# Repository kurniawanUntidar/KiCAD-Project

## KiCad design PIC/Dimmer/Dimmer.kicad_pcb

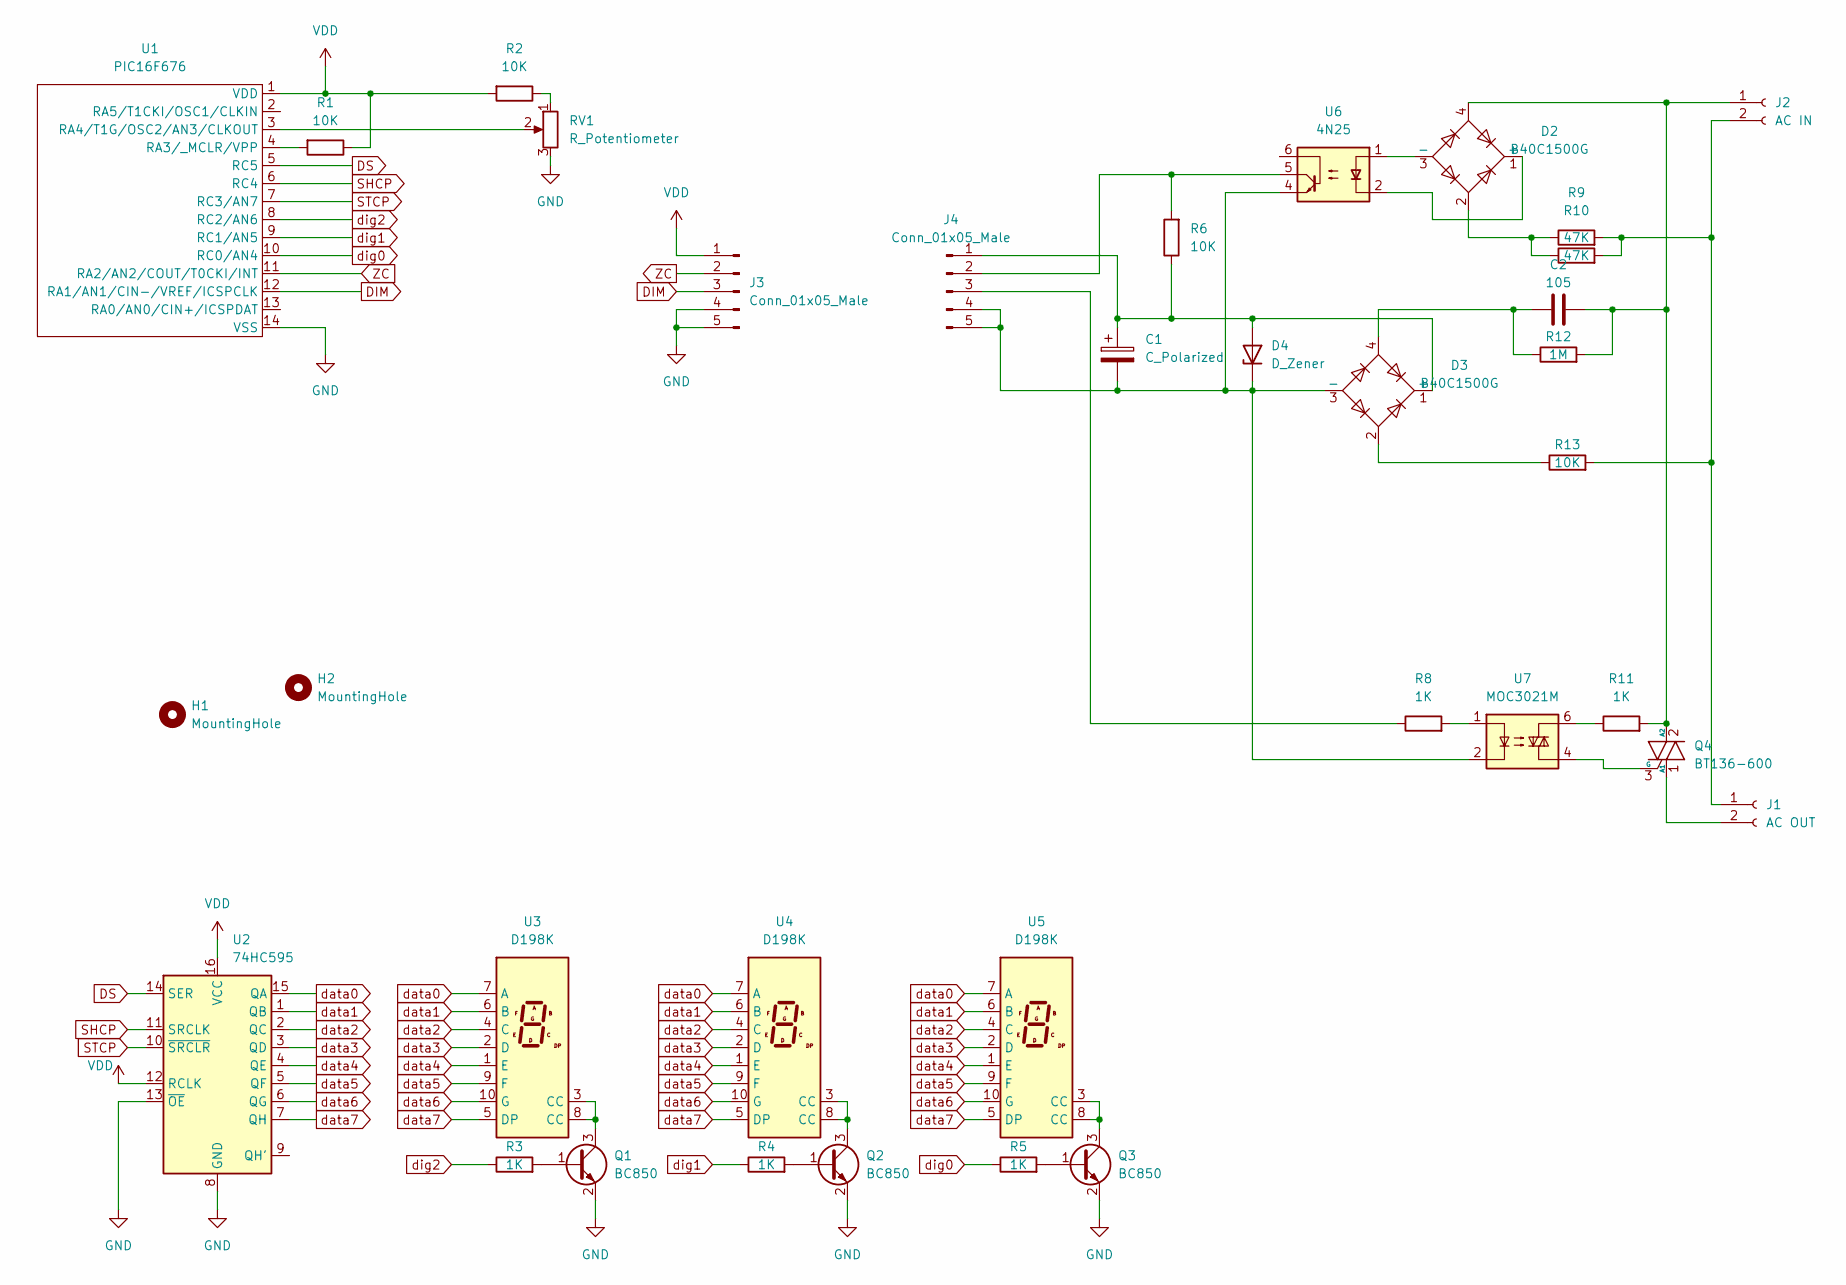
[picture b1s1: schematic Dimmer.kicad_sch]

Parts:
C1: C_Polarized; CP_Radial_D6.3mm_P2.50mm
C2: 105; C_Axial_L5.1mm_D3.1mm_P12.50mm_Horizontal
D2, D3: B40C1500G; Diode_Bridge_Round_D9.8mm
D4: D_Zener; D_DO-34_SOD68_P7.62mm_Horizontal
H1, H2: MountingHole; MountingHole_2.5mm_Pad_Via
J1: AC OUT; TerminalBlock_Phoenix_MKDS-1,5-2_1x02_P5.00mm_Horizontal
J2: AC IN; TerminalBlock_Phoenix_MKDS-1,5-2_1x02_P5.00mm_Horizontal
J3, J4: Conn_01x05_Male; PinHeader_1x05_P2.54mm_Vertical
Q1, Q2, Q3: BC850; SOT-23
Q4: BT136-600; TO-220-3_Vertical
R1, R2, R6: 10K; R_1206_3216Metric
R3, R4, R5, R8, R11: 1K; R_1206_3216Metric
R9, R10: 47K; R_1206_3216Metric
R12: 1M; R_Axial_DIN0204_L3.6mm_D1.6mm_P7.62mm_Horizontal
R13: 10K; R_Axial_DIN0204_L3.6mm_D1.6mm_P7.62mm_Horizontal
RV1: R_Potentiometer; Potentiometer_Bourns_3266Z_Horizontal
U1: PIC16F676; SOIC-14_3.9x8.7mm_P1.27mm
U2: 74HC595; SOIC-16_3.9x9.9mm_P1.27mm
U3, U4, U5: D198K; D1X8K
U6: 4N25; DIP-6_W7.62mm
U7: MOC3021M; DIP-6_W7.62mm

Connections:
DIM: J3.3, U1.12 (RA1/AN1/CIN-/VREF/ICSPCLK)
DS: U1.5 (RC5), U2.14 (SER)
GND: J3.4, J3.5, Q1.2 (E), Q2.2 (E), Q3.2 (E), RV1.3, U1.14 (VSS), U2.8 (GND), U2.13 (~OE)
unnamed: C1.1, D3.1 (+), D4.2 (A), J4.1, R6.1
unnamed: C1.2, D3.3 (-), D4.1 (K), J4.4, J4.5, U6.4, U7.2
unnamed: C2.1, D3.4, R12.1
unnamed: C2.2, D2.4, J2.1, Q4.2 (A2), R11.2, R12.2
unnamed: D2.1 (+), U6.2
unnamed: D2.2, R9.1, R10.1
unnamed: D2.3 (-), U6.1
unnamed: D3.2, R13.1
unnamed: J1.1, J2.2, R9.2, R10.2, R13.2
unnamed: J1.2, Q4.1 (A1)
unnamed: J4.2, R6.2, U6.5
unnamed: J4.3, R8.1
unnamed: Q1.1 (B), R3.2
unnamed: Q1.3 (C), U3.3 (CC), U3.8 (CC)
unnamed: Q2.1 (B), R4.2
unnamed: Q2.3 (C), U4.3 (CC), U4.8 (CC)
unnamed: Q3.1 (B), R5.2
unnamed: Q3.3 (C), U5.3 (CC), U5.8 (CC)
unnamed: Q4.3 (G), U7.4
unnamed: R1.2, U1.4 (RA3/_MCLR/VPP)
unnamed: R2.1, RV1.1
unnamed: R8.2, U7.1
unnamed: R11.1, U7.6
unnamed: RV1.2, U1.3 (RA4/T1G/OSC2/AN3/CLKOUT)
SHCP: U1.6 (RC4), U2.11 (SRCLK)
STCP: U1.7 (RC3/AN7), U2.10 (~SRCLR)
VDD: J3.1, R1.1, R2.2, U1.1 (VDD), U2.12 (RCLK), U2.16 (VCC)
ZC: J3.2, U1.11 (RA2/AN2/COUT/T0CKI/INT)
data0: U2.15 (QA), U3.7 (A), U4.7 (A), U5.7 (A)
data1: U2.1 (QB), U3.6 (B), U4.6 (B), U5.6 (B)
data2: U2.2 (QC), U3.4 (C), U4.4 (C), U5.4 (C)
data3: U2.3 (QD), U3.2 (D), U4.2 (D), U5.2 (D)
data4: U2.4 (QE), U3.1 (E), U4.1 (E), U5.1 (E)
data5: U2.5 (QF), U3.9 (F), U4.9 (F), U5.9 (F)
data6: U2.6 (QG), U3.10 (G), U4.10 (G), U5.10 (G)
data7: U2.7 (QH), U3.5 (DP), U4.5 (DP), U5.5 (DP)
dig0: R5.1, U1.10 (RC0/AN4)
dig1: R4.1, U1.9 (RC1/AN5)
dig2: R3.1, U1.8 (RC2/AN6)

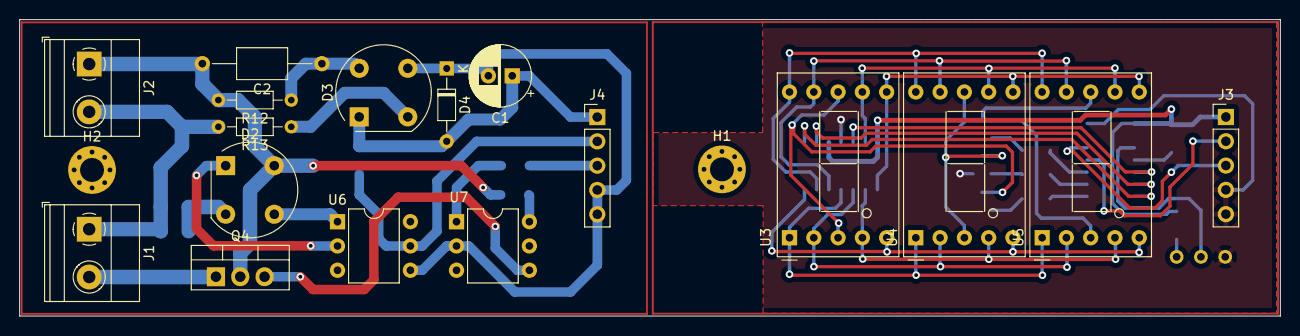
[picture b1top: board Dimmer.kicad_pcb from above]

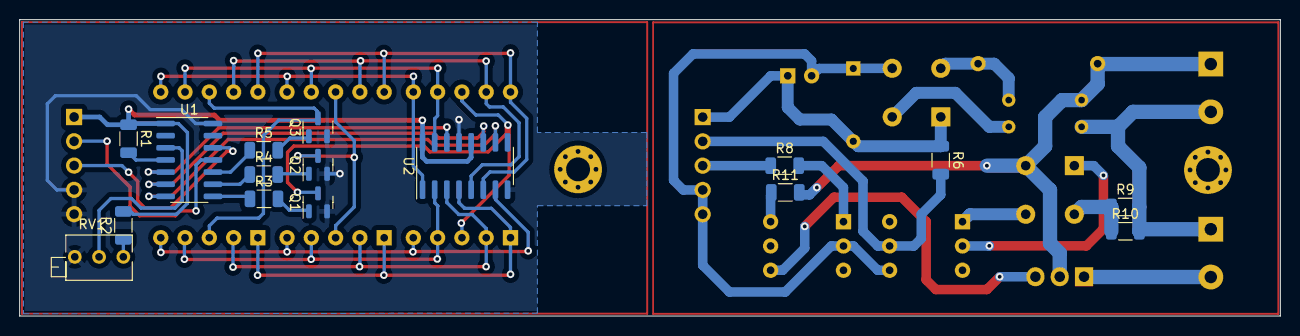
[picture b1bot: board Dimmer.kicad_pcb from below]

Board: 2 copper layers, 131.8 x 31.0 mm, 35 parts (16 on the bottom side), 42 nets.

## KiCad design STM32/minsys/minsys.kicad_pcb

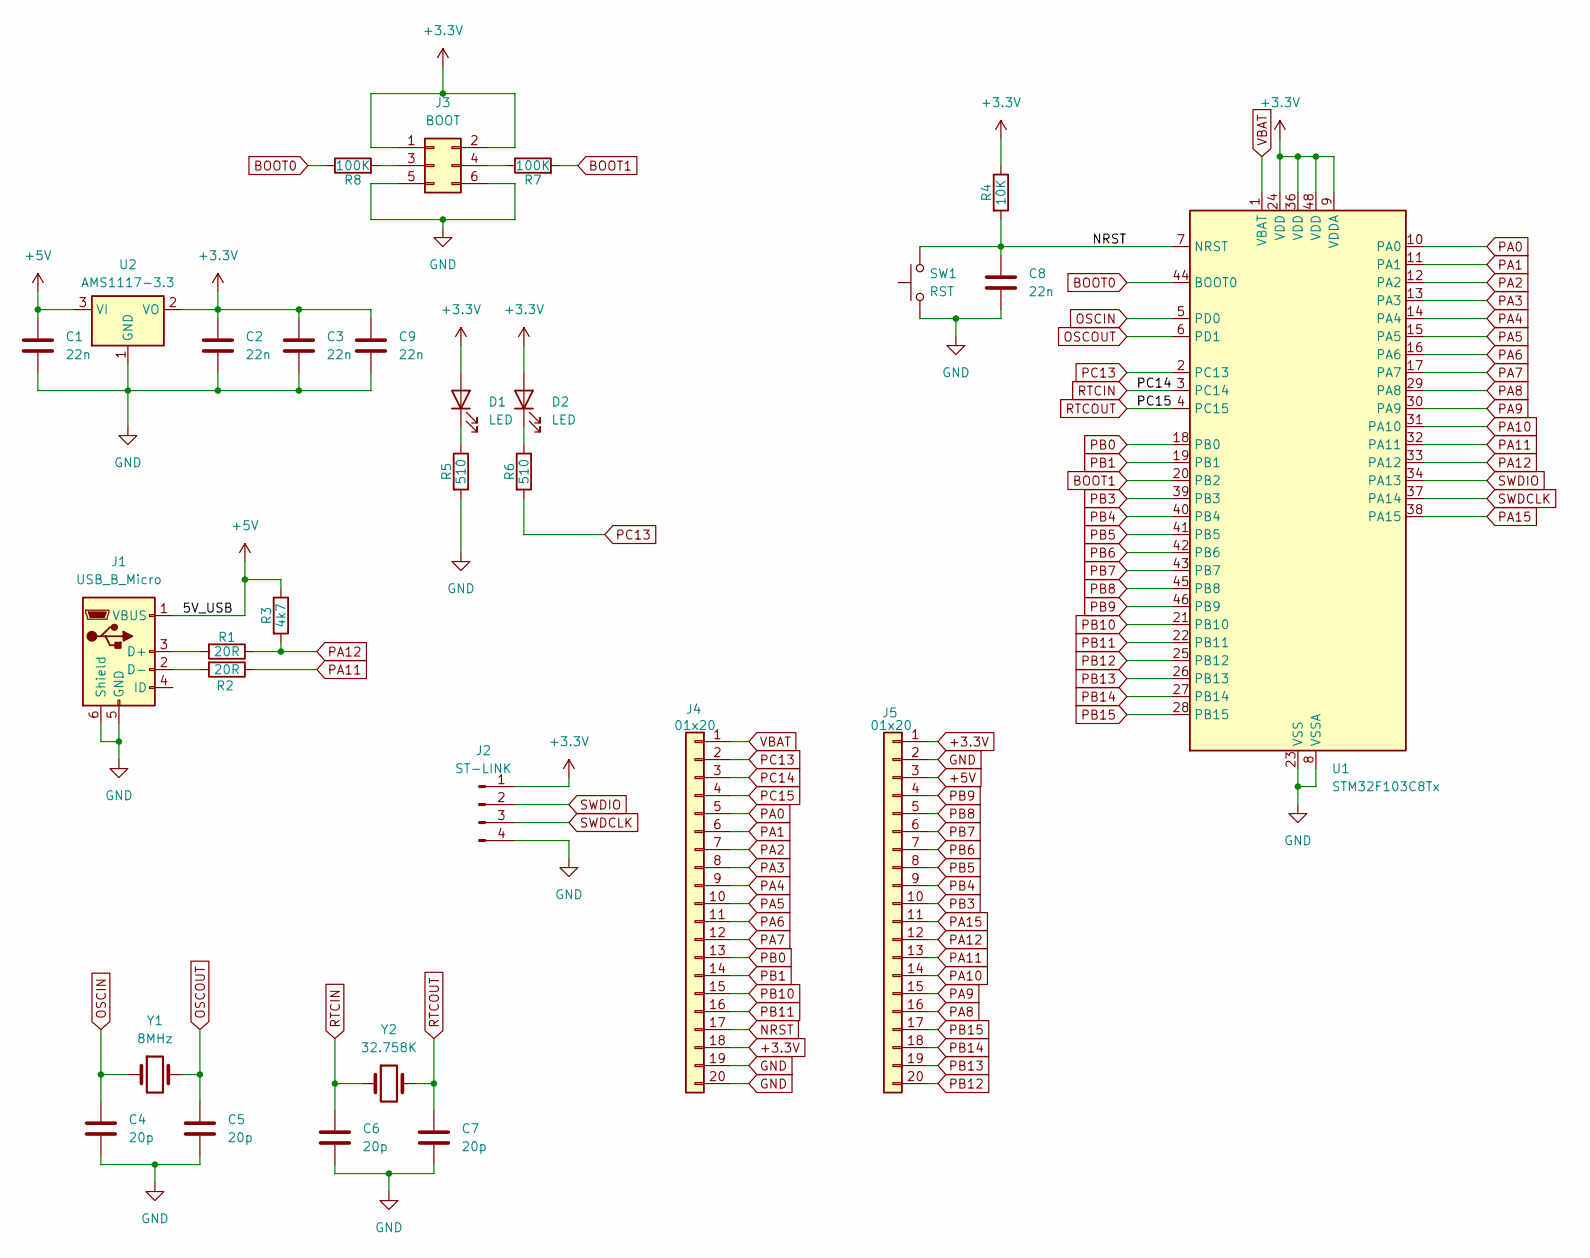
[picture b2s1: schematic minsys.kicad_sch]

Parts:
C1, C2, C3, C8, C9: 22n; C_1206_3216Metric_Pad1.33x1.80mm_HandSolder
C4, C5, C6, C7: 20p; C_1206_3216Metric_Pad1.33x1.80mm_HandSolder
D1, D2: LED; LED_0402_1005Metric_Pad0.77x0.64mm_HandSolder
J1: USB_B_Micro; USB_Micro-B_Amphenol_10118193-0001LF_Horizontal
J2: ST-LINK; JST_EH_B4B-EH-A_1x04_P2.50mm_Vertical
J3: BOOT; PinHeader_2x03_P2.54mm_Vertical
J4, J5: 01x20; PinHeader_1x20_P2.54mm_Vertical
R1, R2: 20R; R_1206_3216Metric_Pad1.30x1.75mm_HandSolder
R3: 4k7; R_1206_3216Metric_Pad1.30x1.75mm_HandSolder
R4: 10K; R_1206_3216Metric_Pad1.30x1.75mm_HandSolder
R5, R6: 510; R_1206_3216Metric_Pad1.30x1.75mm_HandSolder
R7, R8: 100K; R_1206_3216Metric_Pad1.30x1.75mm_HandSolder
SW1: RST; SW_Push_1P1T_NO_CK_KSC6xxG
U1: STM32F103C8Tx; LQFP-48_7x7mm_P0.5mm
U2: AMS1117-3.3; SOT-223-3_TabPin2
Y1: 8MHz; Crystal_HC18-U_Vertical
Y2: 32.758K; Crystal_DS26_D2.0mm_L6.0mm_Horizontal

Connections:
+3.3V: C2.1, C3.1, C9.1, D1.2 (A), D2.2 (A), J2.1, J3.1, J3.2, J4.18, J5.1, R4.1, U1.9 (VDDA), U1.24 (VDD), U1.36 (VDD), U1.48 (VDD), U2.2 (VO)
+5V: C1.1, J1.1 (VBUS), J5.3, R3.1, U2.3 (VI)
BOOT0: R8.1, U1.44 (BOOT0)
BOOT1: R7.2, U1.20 (PB2)
GND: C1.2, C2.2, C3.2, C4.2, C5.2, C6.2, C7.2, C8.2, C9.2, J1.5 (GND), J1.6 (Shield), J2.4, J3.5, J3.6, J4.19, J4.20, J5.2, R5.2, SW1.1, U1.8 (VSSA), U1.23 (VSS), U1.35 (VSS), U1.47 (VSS), U2.1 (GND)
NRST: C8.1, J4.17, R4.2, SW1.2, U1.7 (NRST)
unnamed: D1.1 (K), R5.1
unnamed: D2.1 (K), R6.1
unnamed: J1.3 (D+), R1.2
unnamed: J1.2 (D-), R2.2
unnamed: J3.3, R8.2
unnamed: J3.4, R7.1
OSCIN: C4.1, U1.5 (PD0), Y1.1
OSCOUT: C5.1, U1.6 (PD1), Y1.2
PA0: J4.5, U1.10 (PA0)
PA1: J4.6, U1.11 (PA1)
PA2: J4.7, U1.12 (PA2)
PA3: J4.8, U1.13 (PA3)
PA4: J4.9, U1.14 (PA4)
PA5: J4.10, U1.15 (PA5)
PA6: J4.11, U1.16 (PA6)
PA7: J4.12, U1.17 (PA7)
PA8: J5.16, U1.29 (PA8)
PA9: J5.15, U1.30 (PA9)
PA10: J5.14, U1.31 (PA10)
PA11: J5.13, R2.1, U1.32 (PA11)
PA12: J5.12, R1.1, R3.2, U1.33 (PA12)
PA15: J5.11, U1.38 (PA15)
PB0: J4.13, U1.18 (PB0)
PB1: J4.14, U1.19 (PB1)
PB3: J5.10, U1.39 (PB3)
PB4: J5.9, U1.40 (PB4)
PB5: J5.8, U1.41 (PB5)
PB6: J5.7, U1.42 (PB6)
PB7: J5.6, U1.43 (PB7)
PB8: J5.5, U1.45 (PB8)
PB9: J5.4, U1.46 (PB9)
PB10: J4.15, U1.21 (PB10)
PB11: J4.16, U1.22 (PB11)
PB12: J5.20, U1.25 (PB12)
PB13: J5.19, U1.26 (PB13)
PB14: J5.18, U1.27 (PB14)
PB15: J5.17, U1.28 (PB15)
PC13: J4.2, R6.2, U1.2 (PC13)
PC14: C6.1, J4.3, U1.3 (PC14), Y2.1
PC15: C7.1, J4.4, U1.4 (PC15), Y2.2
SWDCLK: J2.3, U1.37 (PA14)
SWDIO: J2.2, U1.34 (PA13)
VBAT: J4.1, U1.1 (VBAT)

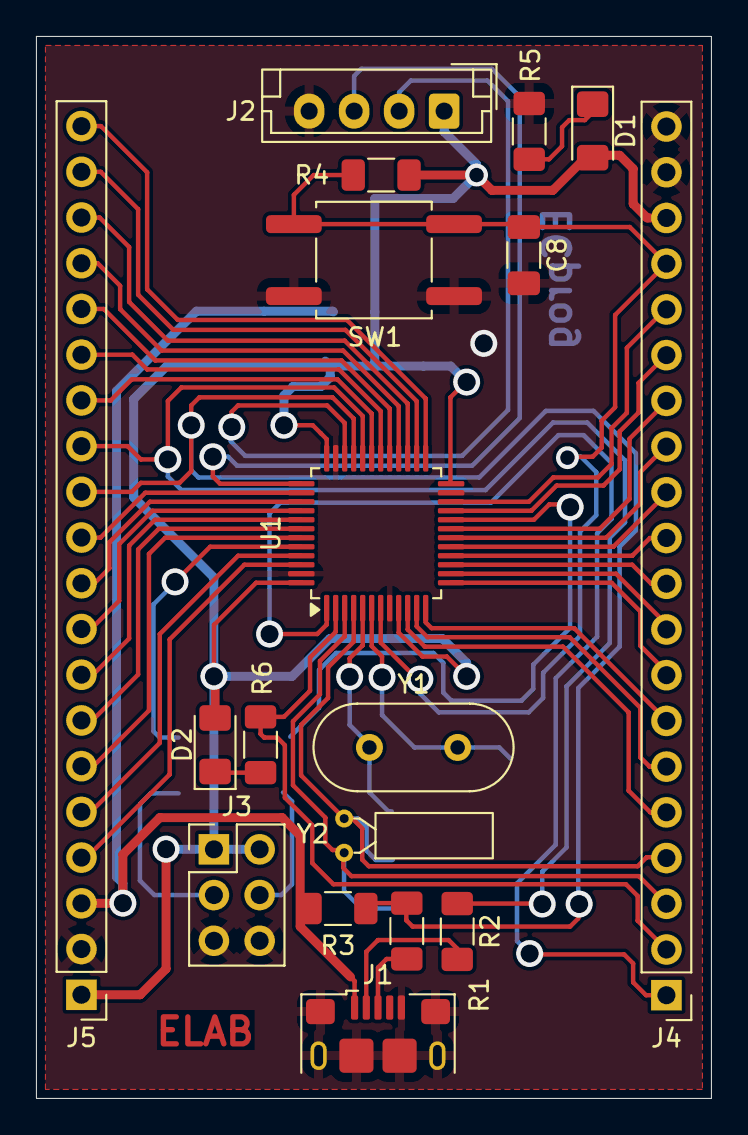
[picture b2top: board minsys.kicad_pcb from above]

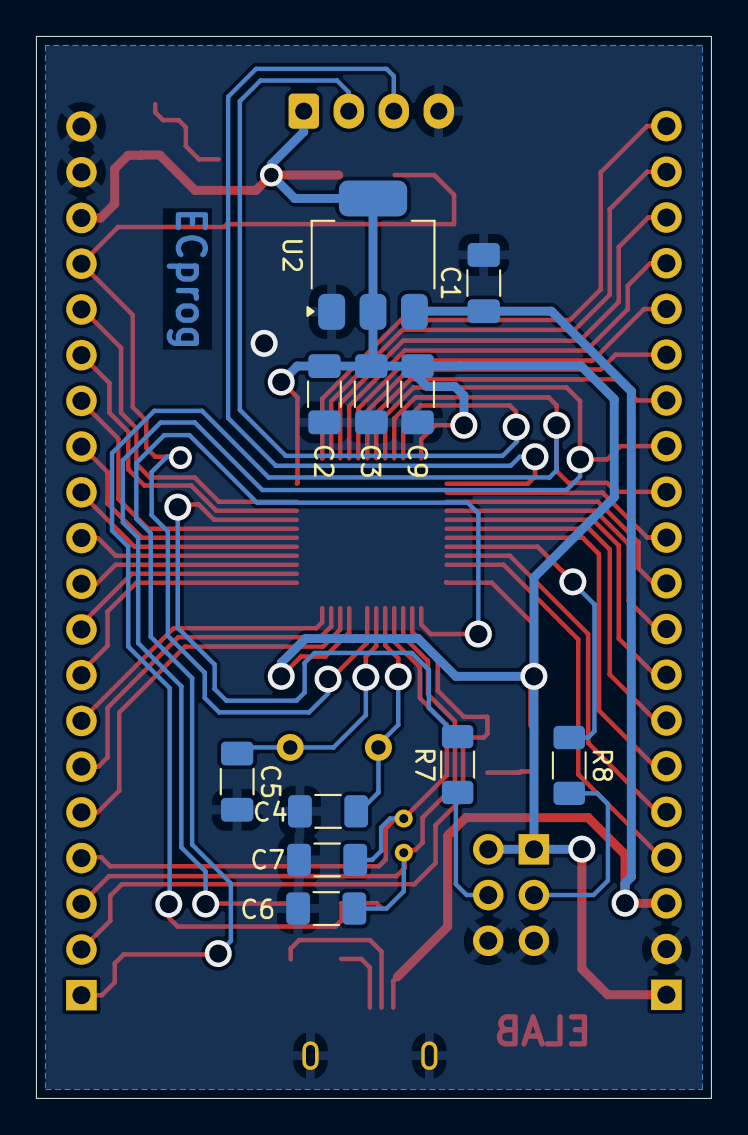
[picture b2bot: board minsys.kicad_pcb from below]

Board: 2 copper layers, 37.5 x 59.0 mm, 29 parts (11 on the bottom side), 49 nets.

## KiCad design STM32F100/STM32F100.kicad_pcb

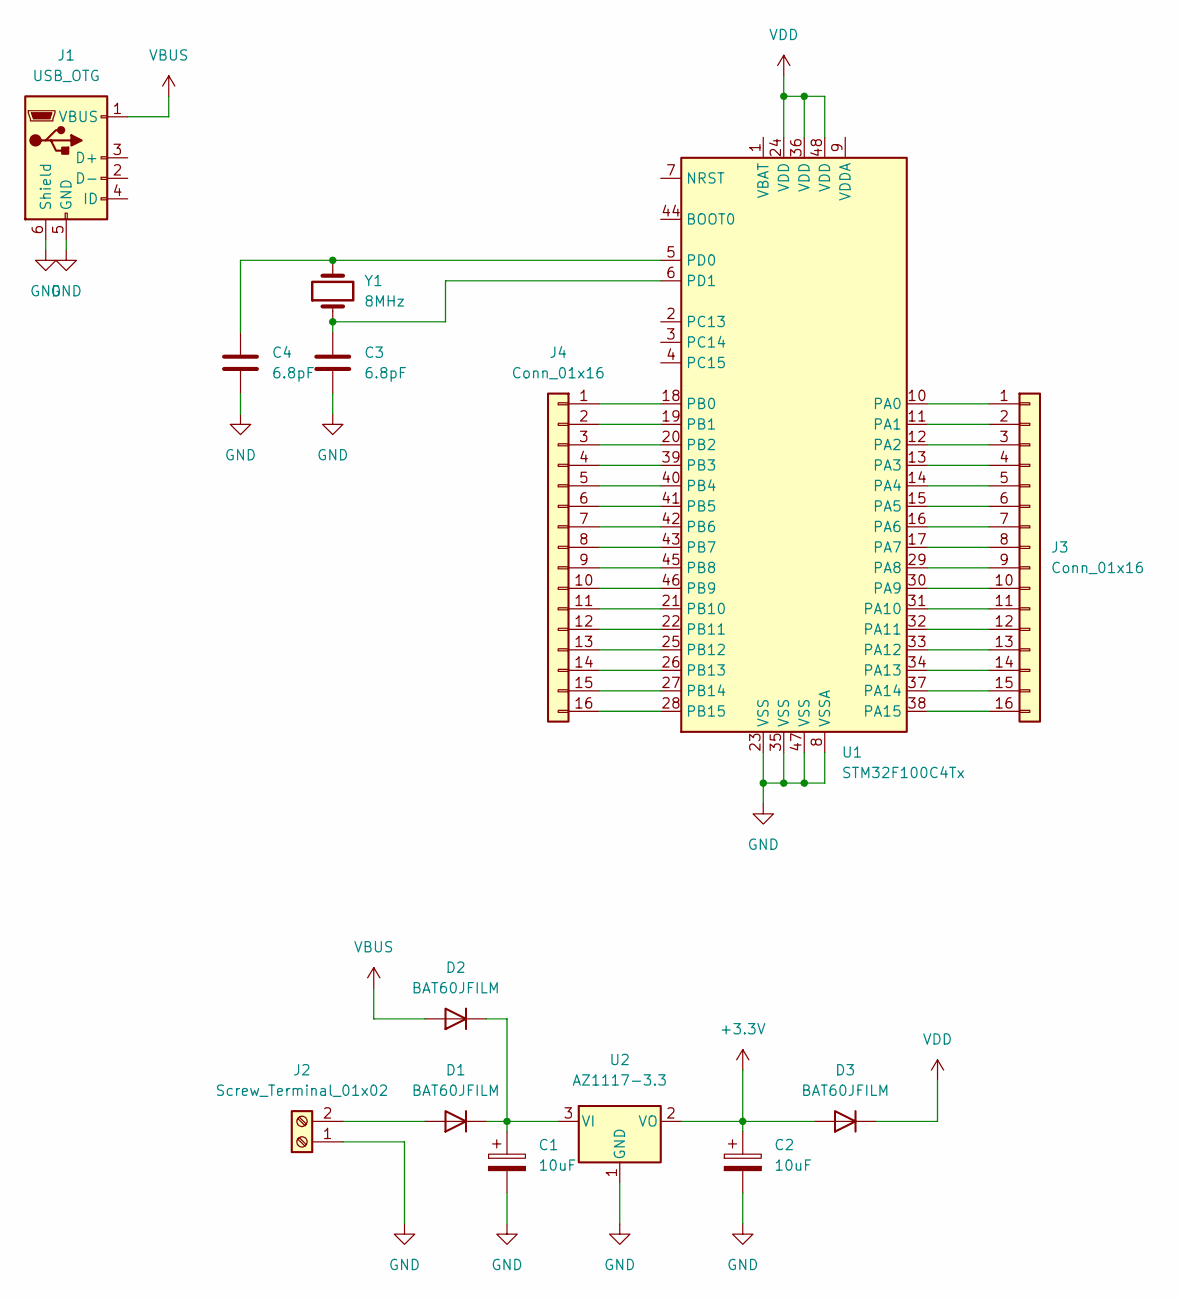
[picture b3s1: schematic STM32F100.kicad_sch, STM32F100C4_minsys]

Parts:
C1, C2: 10uF
C3, C4: 6.8pF; C_0805_2012Metric_Pad1.18x1.45mm_HandSolder
D1: BAT60JFILM
D2, D3: BAT60JFILM; D_2010_5025Metric
J1: USB_OTG; USB_Micro-AB_Molex_47590-0001
J2: Screw_Terminal_01x02; TerminalBlock_Altech_AK300-2_P5.00mm
J3: Conn_01x16
J4: Conn_01x16; Molex_KK-254_AE-6410-16A_1x16_P2.54mm_Vertical
U1: STM32F100C4Tx; LQFP-48_7x7mm_P0.5mm
U2: AZ1117-3.3; SOT-89-3_Handsoldering
Y1: 8MHz; Crystal_HC52-U_Vertical

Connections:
+3.3V: C2.1, D3.2 (A), U2.2 (VO)
GND: C1.2, C2.2, C3.2, C4.2, J1.5 (GND), J1.6 (Shield), J2.1, U1.8 (VSSA), U1.23 (VSS), U1.35 (VSS), U1.47 (VSS), U2.1 (GND)
unnamed: C3.1, U1.6 (PD1), Y1.1
unnamed: C4.1, U1.5 (PD0), Y1.2
unnamed: D1.2 (A), J2.2
unnamed: J3.11, U1.31 (PA10)
unnamed: J3.12, U1.32 (PA11)
unnamed: J3.13, U1.33 (PA12)
unnamed: J3.16, U1.38 (PA15)
unnamed: J4.1, U1.18 (PB0)
unnamed: J4.2, U1.19 (PB1)
unnamed: J4.3, U1.20 (PB2)
unnamed: J4.4, U1.39 (PB3)
unnamed: J4.5, U1.40 (PB4)
unnamed: J3.1, U1.10 (PA0)
unnamed: J3.2, U1.11 (PA1)
unnamed: J3.3, U1.12 (PA2)
unnamed: J3.4, U1.13 (PA3)
unnamed: J3.5, U1.14 (PA4)
unnamed: J3.6, U1.15 (PA5)
unnamed: J3.7, U1.16 (PA6)
unnamed: J3.8, U1.17 (PA7)
unnamed: J4.11, U1.21 (PB10)
unnamed: J4.12, U1.22 (PB11)
unnamed: J4.13, U1.25 (PB12)
unnamed: J4.14, U1.26 (PB13)
unnamed: J4.15, U1.27 (PB14)
unnamed: J4.16, U1.28 (PB15)
unnamed: J3.9, U1.29 (PA8)
unnamed: J3.10, U1.30 (PA9)
unnamed: J3.14, U1.34 (PA13)
unnamed: J3.15, U1.37 (PA14)
unnamed: J4.6, U1.41 (PB5)
unnamed: J4.7, U1.42 (PB6)
unnamed: J4.8, U1.43 (PB7)
unnamed: J4.9, U1.45 (PB8)
unnamed: J4.10, U1.46 (PB9)
unnamed: C1.1, D1.1 (K), D2.1 (K), U2.3 (VI)
VBUS: D2.2 (A), J1.1 (VBUS)
VDD: D3.1 (K), U1.24 (VDD), U1.36 (VDD), U1.48 (VDD)

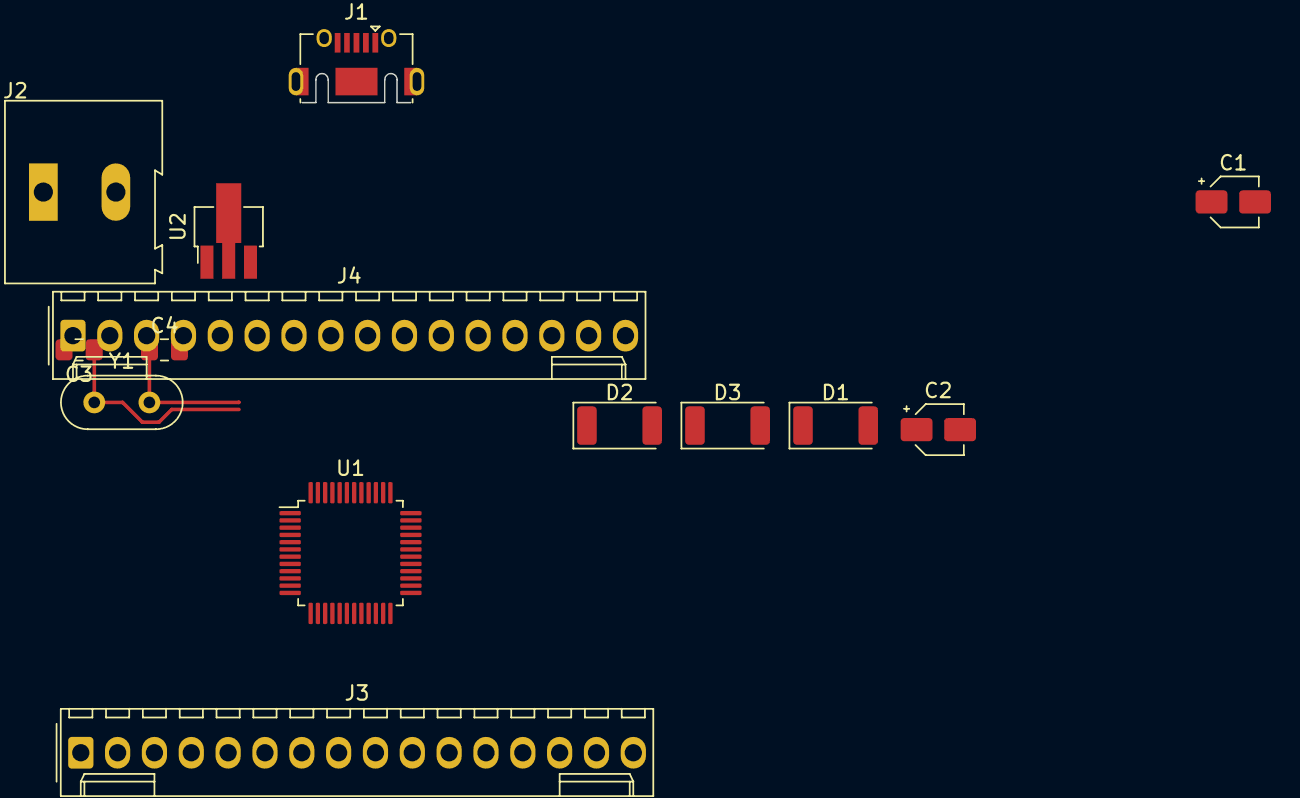
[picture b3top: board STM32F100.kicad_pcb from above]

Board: 2 copper layers, 14 parts (0 on the bottom side), 40 nets.

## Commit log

2023-03-28 Create STM32F100C4 project
    Minimum System STM32F100C
2023-03-28 Add AMS1117 3.3V
    add 3.3V voltage regulator
2023-03-28 Add IO pin header
    Add IO Pinheader
2026-02-22 add minsys
2026-02-23 edit pcb
2026-02-24 add minsys.kicad(copy).pcb
2026-05-03 add PIC
2026-05-03 add elab lib
2026-05-06 add board file
2026-05-10 finish PCB
